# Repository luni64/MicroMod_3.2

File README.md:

# MM32
Experimental NXP MK20DX256 controller board compatible to the SparkFun MicroMod (https://www.sparkfun.com/micromod) system and the [PJRC Teensyduino](https://www.pjrc.com/teensy/teensyduino.html) ecosystem. I.e., the board fits on the SparkFun MicroMod carriers and is able to run firmware written for a Teensy 3.2.

The MM32 board utilizes the un-brickable PJRC bootloader, preprogrammed on the MKL02 chip. Please note: You need to buy the bootloader directly from PJRC (https://www.pjrc.com/store/ic_mkl02.html). It won't work with an empty MKL02.

See here https://github.com/luni64/mmStep for a compatible MicroMode stepper driver board.

## Key features:
- Contiguous **8bit port** routed to BUS0-BUS7 (Teensy: PTD0 - PTD7)
- **Two differential ADCs** mapped onto A0/A1 and ADC_D+ ADC_D-
- **True DAC** on PWM_0
- Two **UARTS** (Serial1, Serial2)
- **SPI** interface
- **CAN** Bus
- **Real time clock (RTC)**: 32.679KHz crystal and V_Bat / BAT_VIN/3
supported
- SWD_DIO, SWD_CKL, **debug interface** (bootloader chip can be disabled with a solder bridge on the back side)
- LED pin selectable (solder bridge) between D13 and D23
- Layout optimized for hand soldering

## Functional Pinout

## Production data

### PCB
Gerbers and drill files for the 4 layer, 0.8mm board can be found in the [KiCad/production](/KiCad/Production) folder. Production cost at Chinese board houses are currently (12-2020) less than USD 10 for 10 pieces plus shipping.

### Parts
Here a [link](https://octopart.com/bom-tool/5AbwHvxe) to an Octopart BOM
containing live updated prices and availability from major distributors. It also   provides links to datasheets, and technical information and alternative parts.
### Documentation
Schematic, pictures, pinouts and datasheets can be found in the documentation folder.

### Assembly
If you have experience in soldering SMD parts the assembly is straight forward. You don't need any special equipment. A standard 50W soldering iron (I use [that one](https://www.weller-tools.com/professional/EUR/en/Professional/Soldering+technology/Soldering+irons/Low-voltage+soldering+irons/Magnastat/TCP+24+) ) a magnifying glass (something like [this]( https://www.aliexpress.com/i/4000270805536.html)) and cheap head worn loupe glasses (e.g. [those](https://www.amazon.com/AORAEM-Magnifier-Glasses-Light-Extensions/dp/B01AJOD03A/ref=pd_vtp_194_1/145-9533834-3577657?_encoding=UTF8&pd_rd_i=B01AJOD03A&pd_rd_r=63fb740a-9b8e-4cf2-9c06-6a06746b77a2&pd_rd_w=vxmCN&pd_rd_wg=adZVj&pf_rd_p=4f2ab3e8-468a-4a7c-9b91-89d6a9221c29&pf_rd_r=BTKH33K3SHZ2QSCJZ0XT&psc=1&refRID=BTKH33K3SHZ2QSCJZ0XT)) are absolutely sufficient. Don't use a pinpoint soldering tip. You need something to transport heat quickly which is best done by a relatively large tip as shown in the video below. 

The only part I found a bit difficult to solder is the small bootloader chip (QFN16). The pads on the board are sufficiently long to solder the chip by hand in principle. However, it is a bit tedious to precisely align the chip to the pads. Start with soldering one pin, then control position and align the chip until it fits. It is helpful to apply some flux paste below the chip which will keep it in place during the alignment. Alternatively you can solder it with a hot air gun.

The rest of the parts are small but easy to solder.

Here a video showing the assembly:

## Firmware

The [firmware folder](/Firmware) contains a header defining the
MicroMod <-> Teensyduino pin mappings and a helper class to access the
8bit BUS.

## Debug configuration

You can disable the bootloader by grounding its reset pin. To do so you
need to close the solder bridge on the bottom of the board as shown here:

You can then connect a debug probe (e.g. a JLink-Mini EDU) to the debug
header on the carrier board.

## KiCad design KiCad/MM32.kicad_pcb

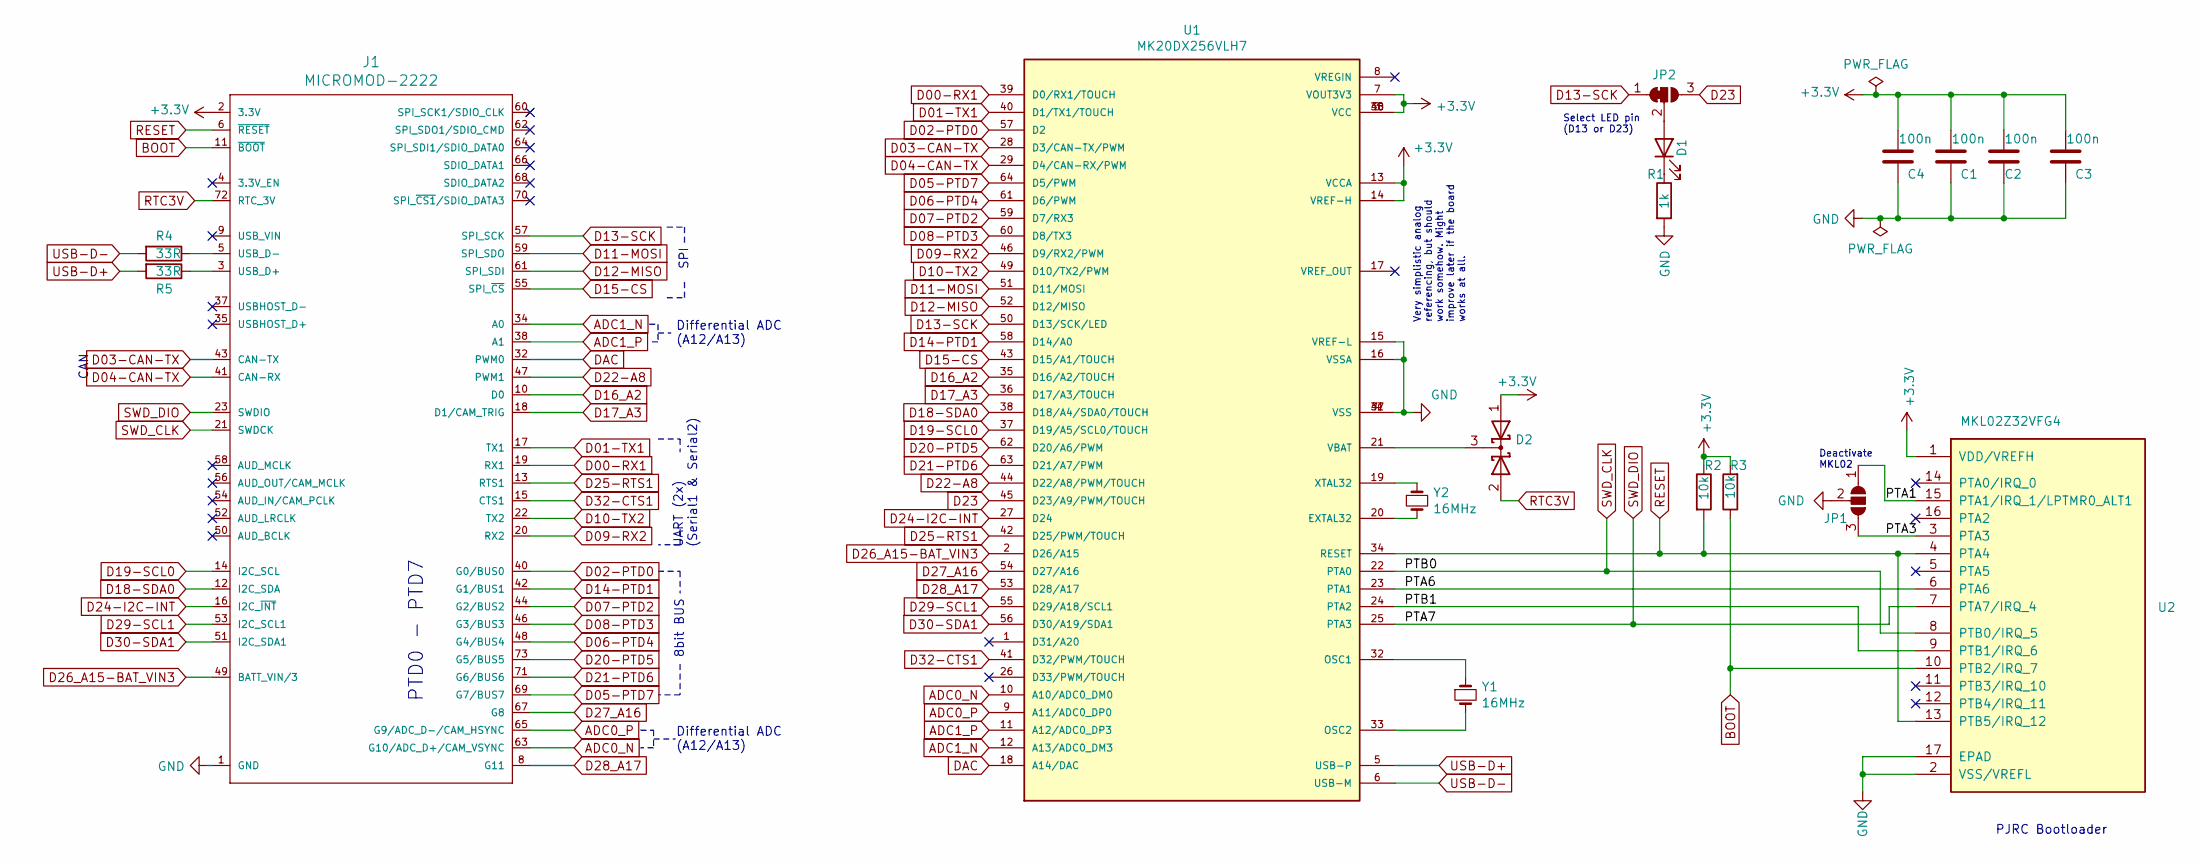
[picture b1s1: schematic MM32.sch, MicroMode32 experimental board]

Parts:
C1, C2, C3, C4: 100n; C_0603_1608Metric_Pad1.08x0.95mm_HandSolder
D1: LED; LED_0805_2012Metric_Pad1.15x1.40mm_HandSolder
D2: D_Schottky_x2_KCom_AAK; SOT-23
J1: MICROMOD-2222; M.2-CARD-E-22
JP1: SolderJumper_3_Open; SolderJumper-3_P1.3mm_Open_RoundedPad1.0x1.5mm
JP2: SolderJumper_3_Bridged12; SolderJumper-3_P1.3mm_Bridged12_RoundedPad1.0x1.5mm
R1: 1k; R_0603_1608Metric_Pad1.05x0.95mm_HandSolder
R2, R3: 10k; R_0603_1608Metric_Pad1.05x0.95mm_HandSolder
R4, R5: 33R; R_0603_1608Metric_Pad1.05x0.95mm_HandSolder
U1: MK20DX256VLH7; QFP50P1200X1200X160-64N
U2: MKL02Z32VFG4; QFN-16-1EP_3x3mm_P0.5mm_EP1.9x1.9mm
Y1, Y2: 16MHz; OSC_XRCHA16M000F0A01R0

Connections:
+3V3: C1.1, C2.1, C3.1, C4.1, D2.1 (A), J1.2 (3.3V), J1.74 (3.3V), R2.1, R3.2, U1.3 (VCC), U1.7 (VOUT3V3), U1.13 (VCCA), U1.14 (VREF-H), U1.30 (VCC), U1.48 (VCC), U2.1 (VDD/VREFH)
/PTA1: JP1.1 (A), U2.15 (PTA1/IRQ_1/LPTMR0_ALT1)
/PTA3: JP1.3 (B), U2.3 (PTA3)
/PTA6: U1.23 (PTA1), U2.6 (PTA6)
/PTB1: U1.24 (PTA2), U2.9 (PTB1/IRQ_6)
ADC0_N: J1.63 (G10/ADC_D+/CAM_VSYNC), U1.10 (A10/ADC0_DM0)
ADC0_P: J1.65 (G9/ADC_D-/CAM_HSYNC), U1.9 (A11/ADC0_DP0)
ADC1_N: J1.34 (A0), U1.12 (A13/ADC0_DM3)
ADC1_P: J1.38 (A1), U1.11 (A12/ADC0_DP3)
BOOT: J1.11 (~BOOT~), R3.1, U2.10 (PTB2/IRQ_7)
D00-RX1: J1.19 (RX1), U1.39 (D0/RX1/TOUCH)
D01-TX1: J1.17 (TX1), U1.40 (D1/TX1/TOUCH)
D02-PTD0: J1.40 (G0/BUS0), U1.57 (D2)
D03-CAN-TX: J1.43 (CAN-TX), U1.28 (D3/CAN-TX/PWM)
D04-CAN-TX: J1.41 (CAN-RX), U1.29 (D4/CAN-RX/PWM)
D05-PTD7: J1.69 (G7/BUS7), U1.64 (D5/PWM)
D06-PTD4: J1.48 (G4/BUS4), U1.61 (D6/PWM)
D07-PTD2: J1.44 (G2/BUS2), U1.59 (D7/RX3)
D08-PTD3: J1.46 (G3/BUS3), U1.60 (D8/TX3)
D09-RX2: J1.20 (RX2), U1.46 (D9/RX2/PWM)
D10-TX2: J1.22 (TX2), U1.49 (D10/TX2/PWM)
D11-MOSI: J1.59 (SPI_SDO), U1.51 (D11/MOSI)
D12-MISO: J1.61 (SPI_SDI), U1.52 (D12/MISO)
D13-SCK: J1.57 (SPI_SCK), JP2.1 (A), U1.50 (D13/SCK/LED)
D14-PTD1: J1.42 (G1/BUS1), U1.58 (D14/A0)
D15-CS: J1.55 (SPI_~CS~), U1.43 (D15/A1/TOUCH)
D16_A2: J1.10 (D0), U1.35 (D16/A2/TOUCH)
D17_A3: J1.18 (D1/CAM_TRIG), U1.36 (D17/A3/TOUCH)
D18-SDA0: J1.12 (I2C_SDA), U1.38 (D18/A4/SDA0/TOUCH)
D19-SCL0: J1.14 (I2C_SCL), U1.37 (D19/A5/SCL0/TOUCH)
D20-PTD5: J1.73 (G5/BUS5), U1.62 (D20/A6/PWM)
D21-PTD6: J1.71 (G6/BUS6), U1.63 (D21/A7/PWM)
D22-A8: J1.47 (PWM1), U1.44 (D22/A8/PWM/TOUCH)
D23: JP2.3 (B), U1.45 (D23/A9/PWM/TOUCH)
D24-I2C-INT: J1.16 (I2C_~INT~), U1.27 (D24)
D25-RTS1: J1.13 (RTS1), U1.42 (D25/PWM/TOUCH)
D26_A15-BAT_VIN3: J1.49 (BATT_VIN/3), U1.2 (D26/A15)
D27_A16: J1.67 (G8), U1.54 (D27/A16)
D28_A17: J1.8 (G11), U1.53 (D28/A17)
D29-SCL1: J1.53 (I2C_SCL1), U1.55 (D29/A18/SCL1)
D30-SDA1: J1.51 (I2C_SDA1), U1.56 (D30/A19/SDA1)
D32-CTS1: J1.15 (CTS1), U1.41 (D32/PWM/TOUCH)
DAC: J1.32 (PWM0), U1.18 (A14/DAC)
GND: C1.2, C2.2, C3.2, C4.2, J1.1 (GND), J1.7 (GND), J1.33 (GND), J1.36 (GND), J1.39 (GND), J1.45 (GND), J1.75 (GND), JP1.2 (C), R1.2, U1.4 (VSS), U1.15 (VREF-L), U1.16 (VSSA), U1.31 (VSS), U1.47 (VSS), U2.2 (VSS/VREFL), U2.17 (EPAD)
unnamed: D1.1 (K), R1.1
unnamed: D1.2 (A), JP2.2 (C)
unnamed: D2.3 (K), U1.21 (VBAT)
unnamed: J1.3 (USB_D+), R5.1
unnamed: J1.5 (USB_D-), R4.1
unnamed: U1.19 (XTAL32), Y2.1
unnamed: U1.20 (EXTAL32), Y2.2
unnamed: U1.32 (OSC1), Y1.1
unnamed: U1.33 (OSC2), Y1.2
RESET: J1.6 (~RESET~), R2.2, U1.34 (RESET), U2.4 (PTA4), U2.13 (PTB5/IRQ_12)
RTC3V: D2.2 (A), J1.72 (RTC_3V)
SWD_CLK: J1.21 (SWDCK), U1.22 (PTA0), U2.8 (PTB0/IRQ_5)
SWD_DIO: J1.23 (SWDIO), U1.25 (PTA3), U2.7 (PTA7/IRQ_4)
USB-D+: R5.2, U1.5 (USB-P)
USB-D-: R4.2, U1.6 (USB-M)

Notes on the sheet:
PTD0 - PTD7
SPI
UART (2x) (Serial1 & Serial2)
8bit BUS
CAN
Deactivate MKL02
PJRC Bootloader
Very simplistic analog referencing, but should work somehow. Might improve later if the board works at all.
Select LED pin (D13 or D23)
Differential ADC (A12/A13)

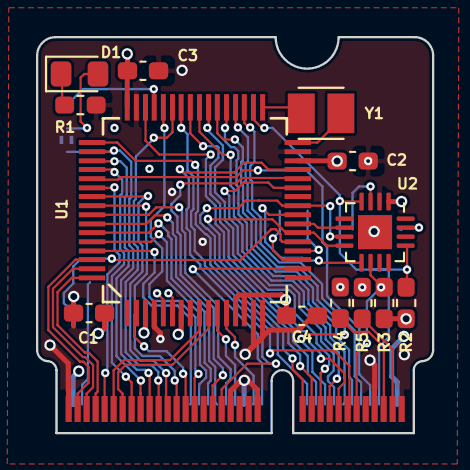
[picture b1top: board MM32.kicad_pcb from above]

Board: 4 copper layers, 22.0 x 22.0 mm, 19 parts (0 on the bottom side), 59 nets.

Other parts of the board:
e: LOGO; logo

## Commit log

2020-12-14 Added schematic
2020-12-14 4 layer design WIP
2020-12-16 finalized 4layer design
2020-12-16 fixed error in schematic
2020-12-16 Solder mask over solder bridges
2020-12-16 Added RTC crystal, and v_bat circuitry. Needs cleanup
2020-12-17 Cleanup board and gerbers
2020-12-17 Added Series Resistors on USB lines
2020-12-18 Rename KiCad files
2020-12-18 Added experimental firmware support
2020-12-18 fixed missing libs
2020-12-18 gitignore
2020-12-19 cleanup
2021-01-07 Added assembly video
2021-01-08 Added info about the debug configuration
